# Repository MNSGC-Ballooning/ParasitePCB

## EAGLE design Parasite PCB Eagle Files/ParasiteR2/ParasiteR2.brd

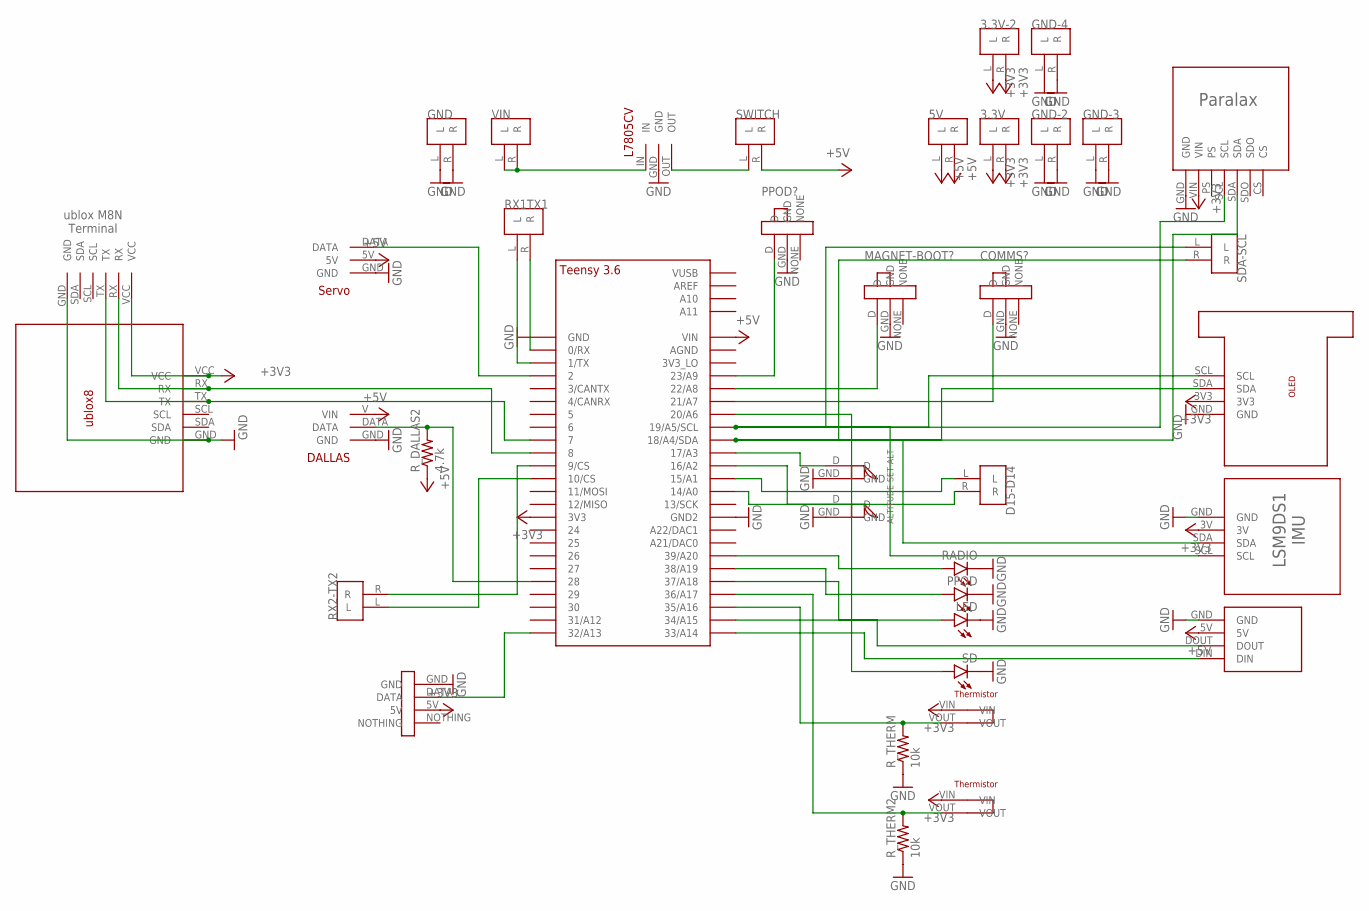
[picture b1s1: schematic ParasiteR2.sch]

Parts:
3.3V, 3.3V-2, 5V: TERMINALBLOCK
ALTITUDE: MOMENTSWITCH
COMMS?: SLIDESWITCH
D15-D14: TERMINALBLOCK
GND: TERMINALBLOCK
GND-2, GND-3, GND-4: TERMINALBLOCK
LED: LED5MM
MAGNET-BOOT?: SLIDESWITCH
PPOD: LED5MM
PPOD?: SLIDESWITCH
RADIO: LED5MM
RX1TX1: RX1 TX1; TERMINALBLOCK
RX2-TX2: TERMINALBLOCK
R_DALLAS2: 4.7k; 0207/12
R_THERM, R_THERM2: 10k; 0207/12
SD: LED5MM
SDA-SCL: TERMINALBLOCK
SET-ALT: MOMENTSWITCH
SWITCH: TERMINALBLOCK
U$1: TEENSY_3.5/3.6_BASIC
U$2: XBEE
U$3: LSM9DS1
U$4: L7805CV
U$5: DALLAS
U$6: MS5607
U$7: SERVO
U$8: UBLOX8
U$9: OLED
U$10: UBLOX8-TERMINALBL
U$11: HONEYWELL
U$20, U$21: THERMISTOR
VIN: TERMINALBLOCK

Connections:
+3V3: 3.3V.L, 3.3V.R, 3.3V-2.L, 3.3V-2.R, U$1.3V3, U$3.3V, U$6.VIN, U$8.VCC, U$9.3V3, U$10.VCC, U$11.5V, U$20.VIN, U$21.VIN
+5V: 5V.L, 5V.R, R_DALLAS2.1, SWITCH.R, U$1.VIN, U$2.5V, U$5.V (VIN), U$7.5V
GND: ALTITUDE.GND, COMMS?.GND, GND.L, GND.R, GND-2.L, GND-2.R, GND-3.L, GND-3.R, GND-4.L, GND-4.R, LED.K (C), MAGNET-BOOT?.GND, PPOD.K (C), PPOD?.GND, RADIO.K (C), R_THERM.1, R_THERM2.1, SD.K (C), SET-ALT.GND, U$1.GND, U$1.GND2, U$2.GND, U$3.GND, U$4.GND, U$5.GND, U$6.GND, U$7.GND, U$8.GND, U$9.GND, U$10.GND, U$11.GND
unnamed: U$1.34/A15, U$2.DOUT
unnamed: U$1.33/A14, U$2.DIN
unnamed: SDA-SCL.R, U$1.18/A4/SDA, U$3.SDA, U$6.SDA, U$9.SDA
unnamed: SDA-SCL.L, U$1.19/A5/SCL, U$3.SCL, U$6.SCL, U$9.SCL
unnamed: U$1.7, U$8.TX, U$10.TX
unnamed: U$1.8, U$8.RX, U$10.RX
unnamed: SWITCH.L, U$4.OUT
unnamed: U$4.IN, VIN.L, VIN.R
unnamed: D15-D14.L, U$1.15/A1
unnamed: R_DALLAS2.2, U$1.28, U$5.DATA
unnamed: U$1.2, U$7.DATA
unnamed: U$1.32/A13, U$11.DATA
unnamed: SD.A, U$1.20/A6
unnamed: RX2-TX2.R, U$1.9/CS
unnamed: RX2-TX2.L, U$1.10/CS
unnamed: R_THERM.2, U$1.35/A16, U$20.VOUT
unnamed: R_THERM2.2, U$1.36/A17, U$21.VOUT
unnamed: RX1TX1.R, U$1.0/RX
unnamed: RX1TX1.L, U$1.1/TX
unnamed: PPOD?.D, U$1.23/A9
unnamed: MAGNET-BOOT?.D, U$1.22/A8
unnamed: SET-ALT.D, U$1.17/A3
unnamed: ALTITUDE.D, U$1.16/A2
unnamed: COMMS?.D, U$1.21/A7
unnamed: RADIO.A, U$1.39/A20
unnamed: PPOD.A, U$1.38/A19
unnamed: LED.A, U$1.37/A18
unnamed: D15-D14.R, U$1.14/A0

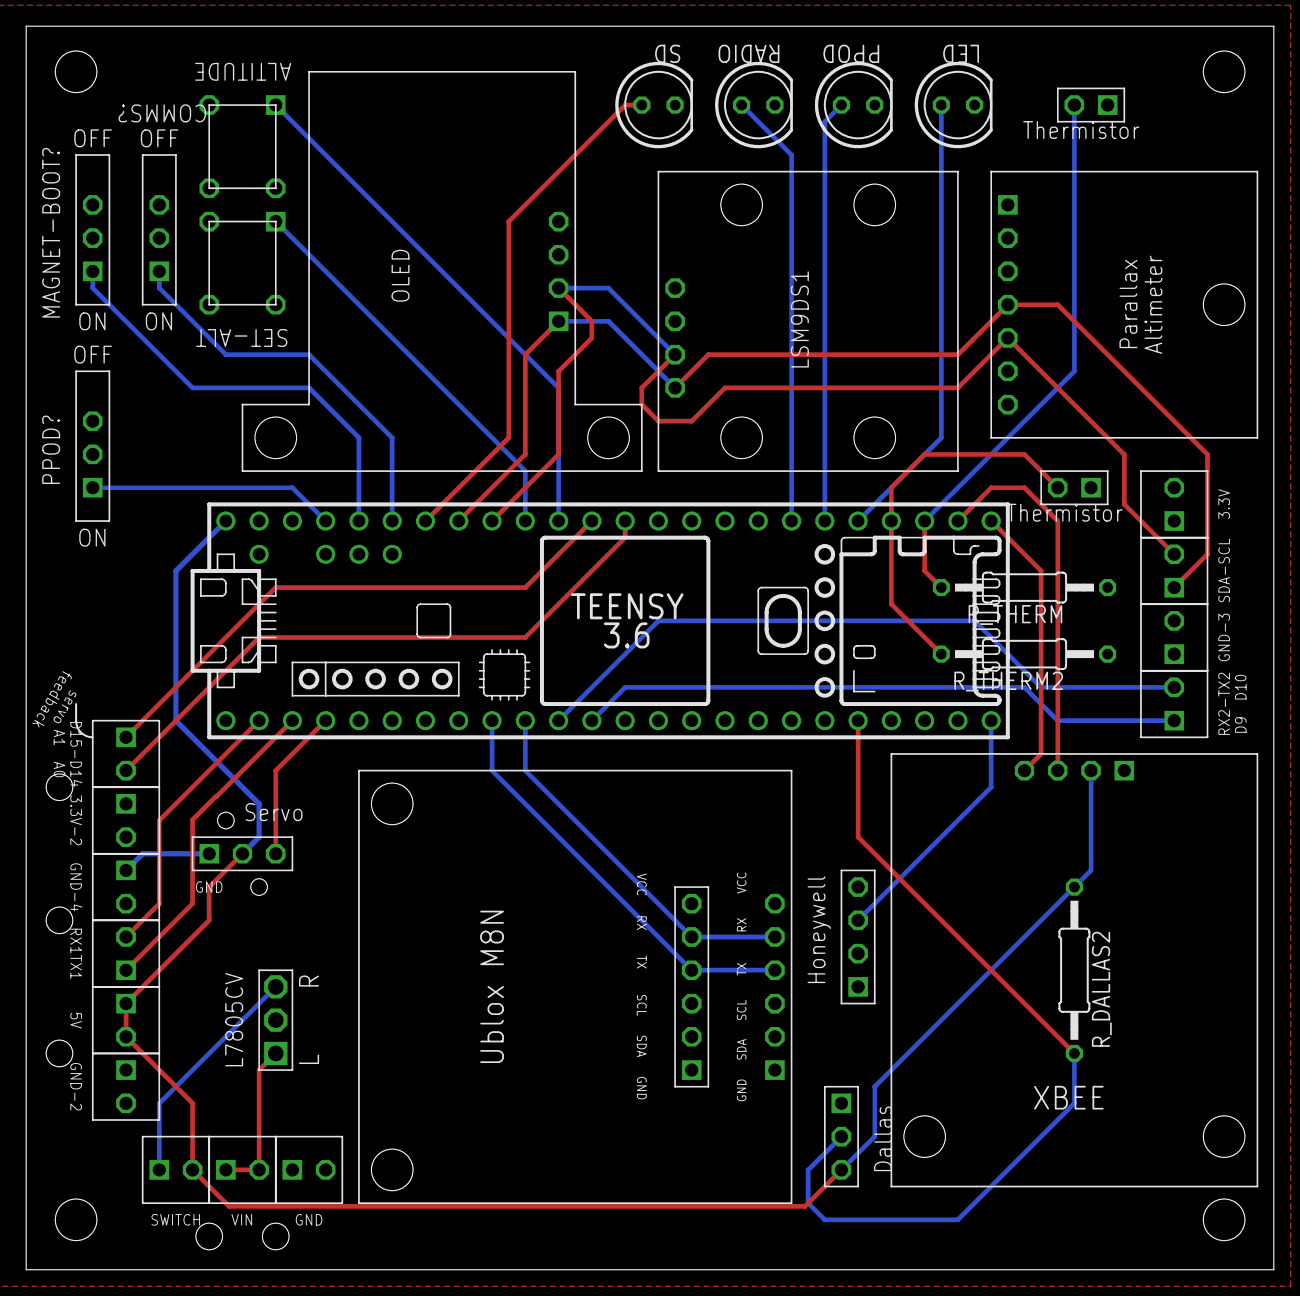
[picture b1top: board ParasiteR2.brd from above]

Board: 2 copper layers, 95.2 x 94.9 mm, 38 parts (0 on the bottom side), 31 nets.

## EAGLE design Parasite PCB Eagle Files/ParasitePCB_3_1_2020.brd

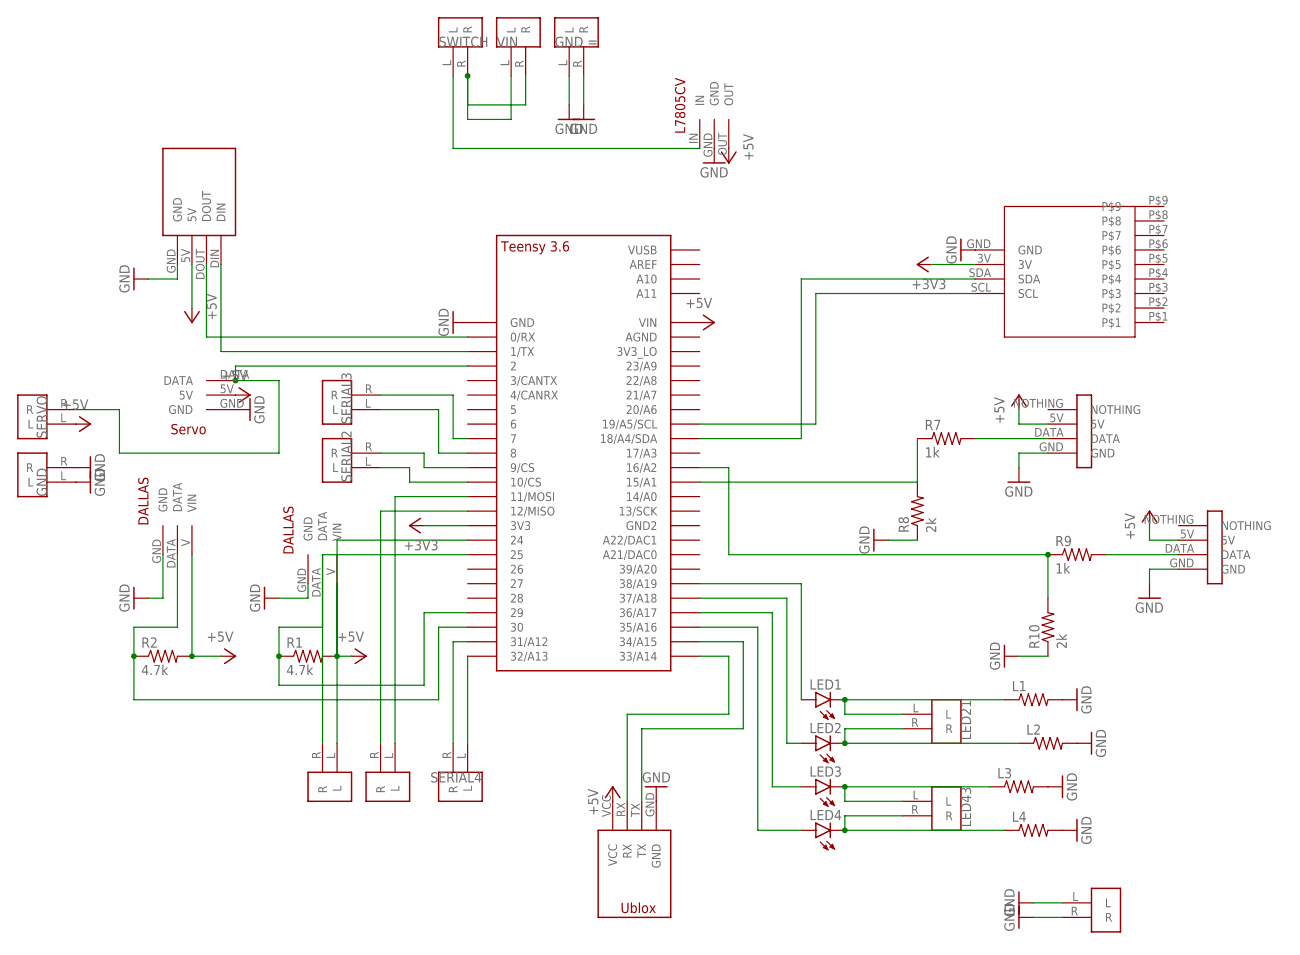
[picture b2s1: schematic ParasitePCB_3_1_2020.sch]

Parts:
HELLO: L7805CV
L1, L2, L3, L4: R-US_0207/12; 0207/12
LED1, LED2, LED3, LED4: LED5MM
LED34: TERMINALBLOCK
R1, R2: 4.7k; 0207/12
R7, R9: 1k; 0207/12
R8, R10: 2k; 0207/12
SERIAL4: TERMINALBLOCK
SERVO: SERVO
U$1: TEENSY_3.5/3.6_BASIC
U$2, U$12: DALLAS
U$3: UBLOX
U$4, U$5, U$6, U$7, U$8, U$9, U$10, U$16, U$17, U$18, U$19: TERMINALBLOCK
U$11: LSM9DS1
U$13, U$14: HONEYWELL
U$15: XBEE

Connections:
+3V3: U$1.3V3, U$11.3V
+5V: HELLO.OUT, R1.2, R2.2, SERVO.5V, U$1.VIN, U$2.V (VIN), U$3.VCC, U$12.V (VIN), U$13.5V, U$14.5V, U$15.5V, U$18.L
GND: HELLO.GND, L1.2, L2.2, L3.2, L4.2, R8.1, R10.1, SERVO.GND, U$1.GND, U$2.GND, U$3.GND, U$6.L, U$6.R, U$8.L, U$8.R, U$11.GND, U$12.GND, U$13.GND, U$14.GND, U$15.GND, U$19.L, U$19.R
unnamed: R2.1, U$1.30, U$12.DATA
unnamed: U$7.R, U$9.L, U$9.R
unnamed: R1.1, U$1.29, U$2.DATA
unnamed: U$1.9/CS, U$4.R
unnamed: LED1.A, U$1.38/A19
unnamed: LED2.A, U$1.37/A18
unnamed: LED3.A, U$1.36/A17
unnamed: LED4.A, U$1.35/A16
unnamed: U$1.0/RX, U$15.DOUT
unnamed: HELLO.IN, U$7.L
unnamed: U$1.10/CS, U$4.L
unnamed: U$1.18/A4/SDA, U$11.SDA
unnamed: L1.1, LED1.K (C), LED34.L
unnamed: L2.1, LED2.K (C), LED34.R
unnamed: L3.1, LED3.K (C), U$10.L
unnamed: L4.1, LED4.K (C), U$10.R
unnamed: U$1.19/A5/SCL, U$11.SCL
unnamed: U$1.7, U$5.R
unnamed: U$1.1/TX, U$15.DIN
unnamed: U$1.8, U$5.L
unnamed: R7.2, U$13.DATA
unnamed: R7.1, R8.2, U$1.15/A1
unnamed: U$1.34/A15, U$3.TX
unnamed: U$1.33/A14, U$3.RX
unnamed: R9.2, U$14.DATA
unnamed: R9.1, R10.2, U$1.16/A2
unnamed: SERVO.DATA, U$1.2, U$18.R
unnamed: SERIAL4.R, U$1.31/A12
unnamed: SERIAL4.L, U$1.32/A13
unnamed: U$1.11/MOSI, U$17.L
unnamed: U$1.12/MISO, U$17.R
unnamed: U$1.24, U$16.L
unnamed: U$1.25, U$16.R

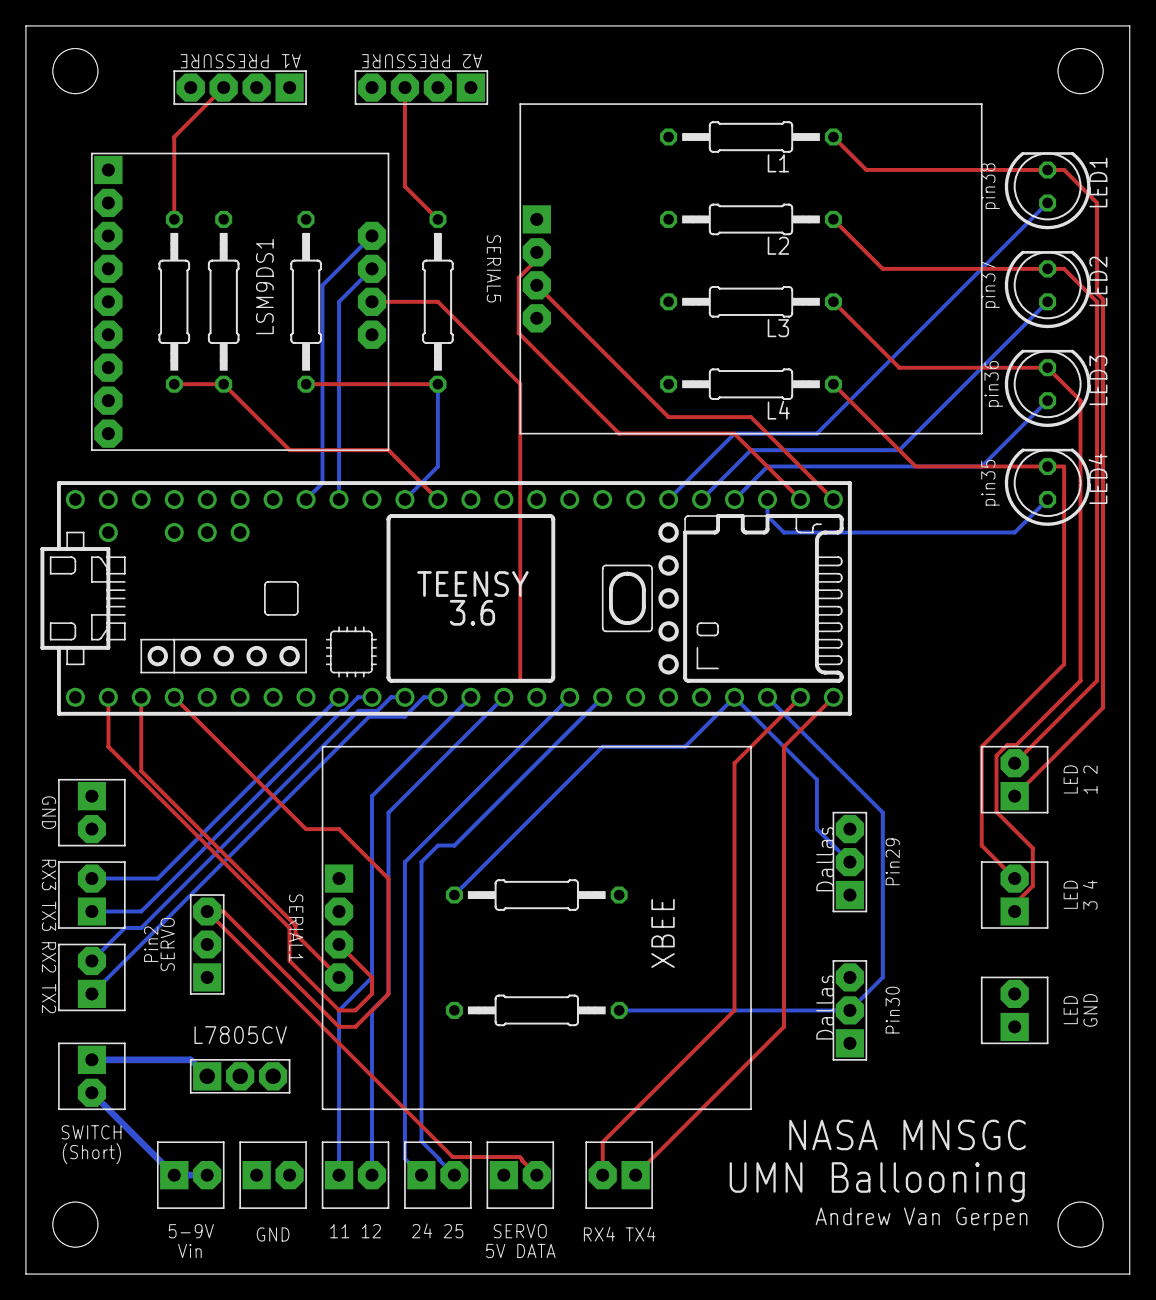
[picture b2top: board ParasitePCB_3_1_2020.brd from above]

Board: 2 copper layers, 85.1 x 96.2 mm, 37 parts (0 on the bottom side), 36 nets.

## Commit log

2020-06-11 ParasiteR2 (2nd revision) eagle files
2020-07-18 Add revision two arduino files
